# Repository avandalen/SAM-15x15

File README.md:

Eagle files for the SAM 15x15 v4 board.

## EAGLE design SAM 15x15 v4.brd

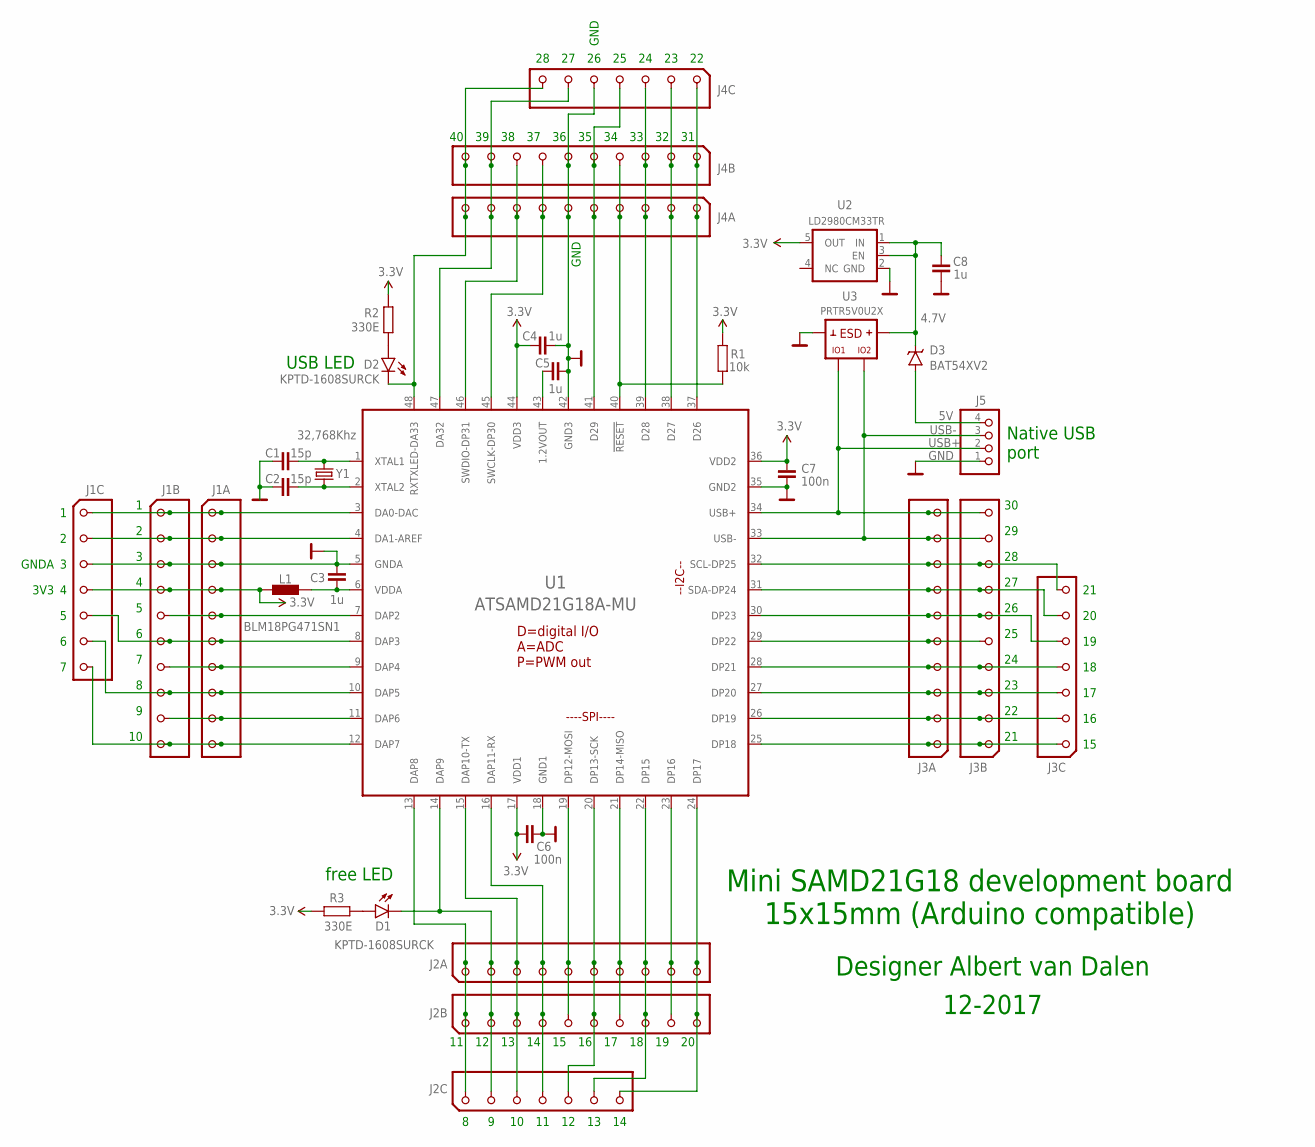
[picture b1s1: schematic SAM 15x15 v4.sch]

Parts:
C1, C2: 15p; 0402-SMALL
C3, C4, C5, C8: 1u; 0402-SMALL
C6, C7: 100n; 0402-SMALL
D1, D2: KPTD-1608SURCK; LED-0603
D3: BAT54XV2; SOD523
J1A, J2A, J3A, J4A: JST-10SAM50; 1.27MM-10P-SAM50
J1B, J2B, J3B, J4B: JST-101X10; 1X10
J1C, J2C, J3C, J4C: SAM7SAM7; SAM7
J5: Header 4p; 1X04
L1: BLM18PG471SN1; ARDUINO_C0603
R1: 10k; 0402-SMALL
R2, R3: 330E; 0402-SMALL
U1: ATSAMD21G18A-MU; QFN-48
U2: LD2980CM33TR; SOT23-5
U3: PRTR5V0U2X; SOT143B
Y1: 32,768Khz; CRYSTAL-SMD-3.2X1.5MM

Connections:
3.3V: C4.2, C6.2, C7.2, J1A.4, J1B.4, J1C.4, L1.1, R1.2, R2.2, R3.2, U1.17 (VDD1), U1.36 (VDD2), U1.44 (VDD3), U2.5 (OUT)
4.7V: C8.2, D3.C, U2.1 (IN), U2.3 (EN), U3.4 (VCC)
5V: D3.A, J5.4
GND: C1.2, C2.2, C3.2, C4.1, C5.1, C6.1, C7.1, C8.1, J1A.3, J1B.3, J1C.3, J4A.6, J4B.6, J4C.5, J5.1, U1.5 (GNDA), U1.18 (GND1), U1.35 (GND2), U1.42 (GND3), U2.2 (GND), U3.1 (GND)
unnamed: D2.A, R2.1
unnamed: J2A.8, J2B.8, J2C.6, U1.22 (DP15)
unnamed: J1A.1, J1B.1, J1C.1, U1.3 (DA0-DAC)
unnamed: J1A.2, J1B.2, J1C.2, U1.4 (DA1-AREF)
unnamed: J1A.5, J1B.5, U1.7 (DAP2)
unnamed: J1A.6, J1B.6, J1C.5, U1.8 (DAP3)
unnamed: J1A.7, J1B.7, U1.9 (DAP4)
unnamed: J2A.3, J2B.3, J2C.3, U1.15 (DAP10-TX)
unnamed: J1A.8, J1B.8, J1C.6, U1.10 (DAP5)
unnamed: D1.C, J2A.2, J2B.2, J2C.2, U1.14 (DAP9)
unnamed: J2A.1, J2B.1, J2C.1, U1.13 (DAP8)
unnamed: J2A.5, J2B.5, U1.19 (DP12-MOSI)
unnamed: J3A.5, J3B.5, U1.29 (DP22)
unnamed: J2A.7, J2B.7, U1.21 (DP14-MISO)
unnamed: J3A.7, J3B.7, J3C.6, U1.31 (SDA-DP24)
unnamed: J2A.9, J2B.9, U1.23 (DP16)
unnamed: J3A.1, J3B.1, J3C.1, U1.25 (DP18)
unnamed: J3A.2, J3B.2, J3C.2, U1.26 (DP19)
unnamed: J3A.3, J3B.3, J3C.3, U1.27 (DP20)
unnamed: J3A.4, J3B.4, J3C.4, U1.28 (DP21)
unnamed: J1A.9, J1B.9, U1.11 (DAP6)
unnamed: J3A.8, J3B.8, J3C.7, U1.32 (SCL-DP25)
unnamed: D1.A, R3.1
unnamed: J2A.6, J2B.6, J2C.5, U1.20 (DP13-SCK)
unnamed: J1A.10, J1B.10, J1C.7, U1.12 (DAP7)
unnamed: J4A.5, J4B.5, J4C.4, U1.41 (D29)
unnamed: J4A.4, J4B.4, R1.1, U1.40 (!RESET!)
unnamed: J4A.7, J4B.7, U1.45 (SWCLK-DP30)
unnamed: J4A.8, J4B.8, U1.46 (SWDIO-DP31)
unnamed: D2.C, J4A.10, J4B.10, J4C.7, U1.48 (RXTXLED-DA33)
unnamed: J4A.3, J4B.3, J4C.3, U1.39 (D28)
unnamed: J4A.2, J4B.2, J4C.2, U1.38 (D27)
unnamed: J2A.10, J2B.10, J2C.7, U1.24 (DP17)
unnamed: J4A.1, J4B.1, J4C.1, U1.37 (D26)
unnamed: J2A.4, J2B.4, J2C.4, U1.16 (DAP11-RX)
unnamed: J3A.6, J3B.6, J3C.5, U1.30 (DP23)
unnamed: J4A.9, J4B.9, J4C.6, U1.47 (DA32)
unnamed: C1.1, U1.1 (XTAL1), Y1.P$2 (2)
unnamed: C2.1, U1.2 (XTAL2), Y1.P$1 (1)
unnamed: C5.2, U1.43 (1.2VOUT)
USB+: J3A.10, J3B.10, J5.2, U1.34 (USB+), U3.3 (IO1)
USB-: J3A.9, J3B.9, J5.3, U1.33 (USB-), U3.2 (IO2)
VDDA: C3.1, L1.2, U1.6 (VDDA)

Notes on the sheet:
Native USB port
USB LED
free LED
GNDA
3V3
Designer Albert van Dalen
12-2017
GND
Mini SAMD21G18 development board 15x15mm (Arduino compatible)

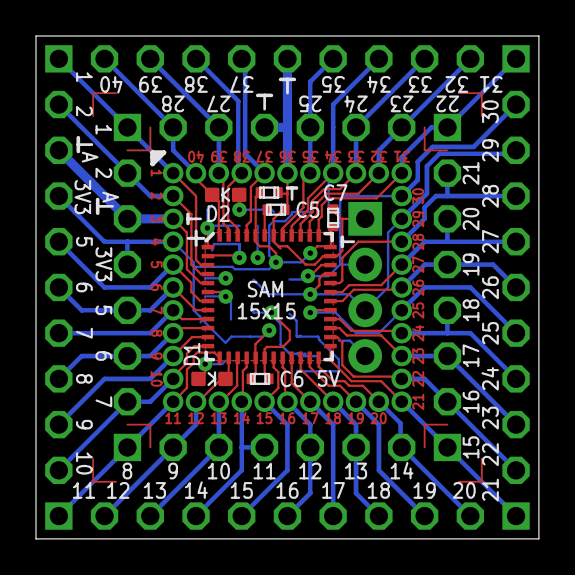
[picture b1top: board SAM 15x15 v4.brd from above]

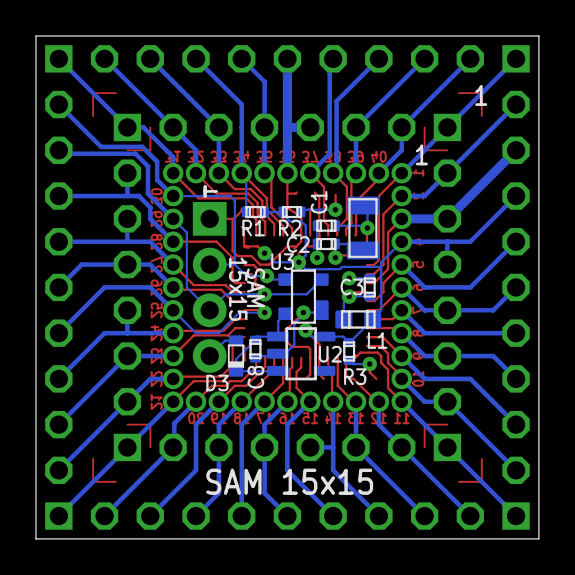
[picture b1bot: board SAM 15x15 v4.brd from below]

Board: 2 copper layers, 27.9 x 27.9 mm, 32 parts (12 on the bottom side), 47 nets.

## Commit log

2021-05-24 Create LICENSE
